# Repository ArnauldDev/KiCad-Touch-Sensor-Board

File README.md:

# Proto Board Touch-Sensor Controller

Top view of the [board with 3D rendering](https://forum.kicad.info/t/simple-tutorial-how-to-create-blender-3d-model-from-kicad/46485) generated with [Blender](https://www.blender.org/), see [Import PCB 3D Models from KiCad](https://extensions.blender.org/add-ons/pcb3d-importer/):

Bottom view of the board and 3D rendering generated with Blender too:

## AT42QT2120

Touch Sensor QTouch [AT42QT2120](https://www.microchip.com/en-us/product/at42qt2120): [view pdf datasheet online](https://ww1.microchip.com/downloads/en/DeviceDoc/doc9634.pdf)

AT42QT2120 is a 10-channel capacitive touch sensor controller with I2C interface.

It is designed for applications such as buttons, sliders, and wheels.

AT42QT2120-SU = 20 pin 0.300 inch wide body SOIC package

[Hole for Backlighting LED - page 13](https://ww1.microchip.com/downloads/aemDocuments/documents/OTH/ApplicationNotes/ApplicationNotes/Atmel-42094-QTouch-Schematic-and-Layout-Checklist_ApplicationNote_AT02259.pdf), see "Figure 3-2. Hole for Backlighting LED"

Example for [AT42QT_API](https://github.com/SmartTech/AT42QT/blob/master/AT42QT_API/QT2120.h)

## Demo board QT1 XPLAINED PRO EXTENSION KIT

Part Number: [ATQT1-XPRO](https://www.microchip.com/en-us/development-tool/ATQT1-XPRO)

[SAM D20 XPLAINED PRO EVALUATION KIT](https://ww1.microchip.com/downloads/aemDocuments/documents/OTH/ProductDocuments/UserGuides/Atmel-42102-SAMD20-Xplained-Pro_User-Guide.pdf)<br>
Part Number: [ATSAMD20-XPRO](https://www.microchip.com/en-us/development-tool/ATSAMD20-XPRO)

---

<br />

## SMD LED reverse mount

LED, Rouge, Vert jaune, CMS - Montage inversé, Rectangulaire, R 20mA, YG 20mA<br>
* [Farnell 2908898](https://fr.farnell.com/rohm/sml-822mv8wt86/led-rouge-jaune-vert-30-25mcd/dp/2908898)
* [Rohm Datasheet](https://fscdn.rohm.com/en/products/databook/datasheet/opto/led/chip_multi/sml-822mv8wt86-e.pdf)

|               Package view                | Reverse mount available, 2-color LED (Yellow-green/Red)                                                                                                                                                                                                                            |
| :---------------------------------------: | :--------------------------------------------------------------------------------------------------------------------------------------------------------------------------------------------------------------------------------------------------------------------------------- |
|  | Part Number: [SML-822MV8WT86](https://www.rohm.com/products/led/chip-leds-multi-color-type/sml-822mv8w-product)<br>SML-82 series is a two-color LED chip LED for back-mounting.<br>Rear mounting enables single-sided mounting, contributing to space saving in the mounting area. |

---

## Driver de LED DC/DC

### PCA9635PW,118

LED-Driver-PCA9635

> Code Commande Farnell : [1854073](https://fr.farnell.com/nxp/pca9635pw-118/driver-de-led-rgba-28-tssop/dp/1854073)
> Quantité 1, Prix (TVA incluse) 2,760€
> Driver LED, Bus I2C, Isolé, 16 bits, 1MHz, Sortie 5,5V/25mA, Entrée 2,3V à 5,5V
> https://fr.aliexpress.com/item/33038992925.html
> https://www.nxp.com/docs/en/data-sheet/PCA9635.pdf

[Breakout PCA9685PW module Servomotor Shield on Aliexpress](https://fr.aliexpress.com/item/1005007462728654.html)

<!--  -->

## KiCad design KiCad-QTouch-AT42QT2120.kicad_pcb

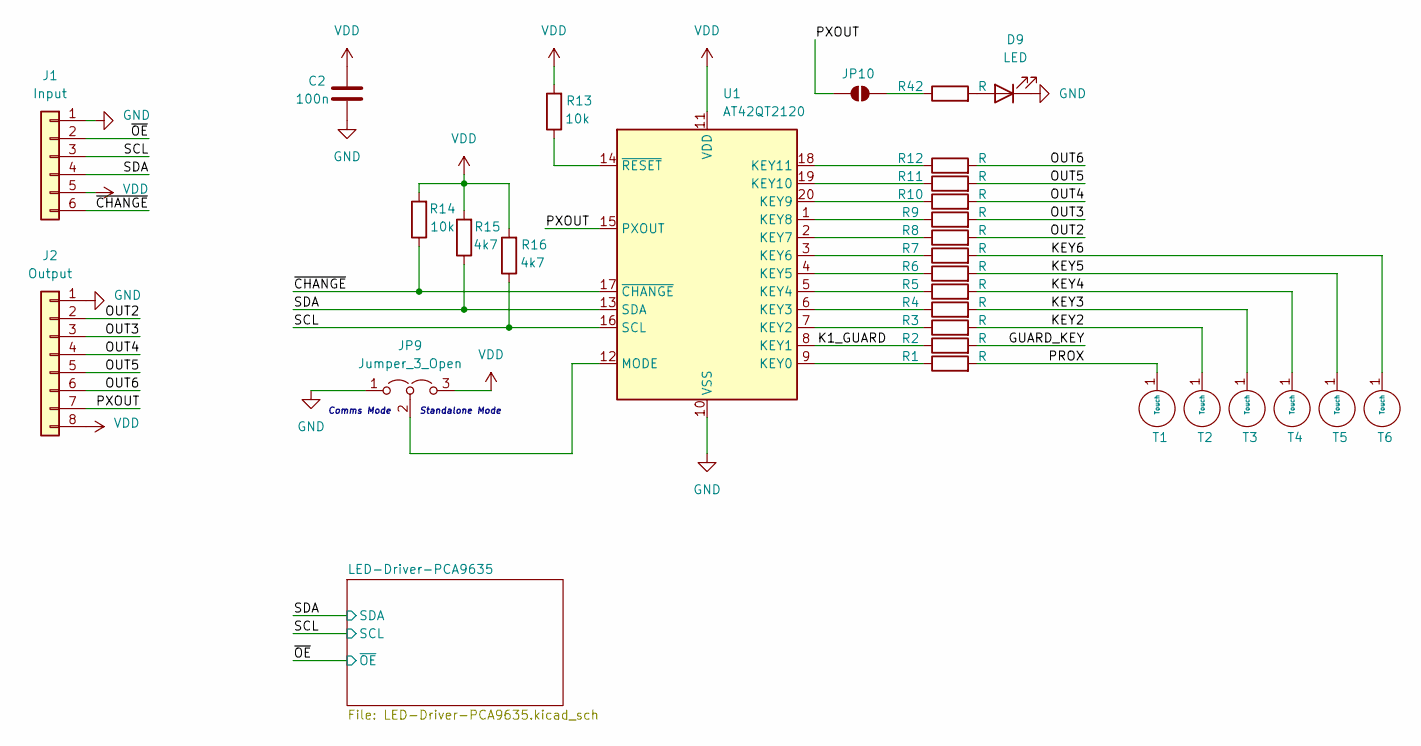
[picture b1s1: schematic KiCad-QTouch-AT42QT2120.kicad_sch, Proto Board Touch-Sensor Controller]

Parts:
C2: 100n; C_0805_2012Metric_Pad1.18x1.45mm_HandSolder
D9: LED; LED_0805_2012Metric_Pad1.15x1.40mm_HandSolder
J1: Input; PinHeader_1x06_P2.54mm_Vertical
J2: Output; PinHeader_1x08_P2.54mm_Vertical
JP9: Jumper_3_Open; SolderJumper-3_P2.0mm_Open_TrianglePad1.0x1.5mm
JP10: SolderJumper_2_Open; SolderJumper-2_P1.3mm_Open_TrianglePad1.0x1.5mm
R1, R2, R3, R4, R5, R6, R7, R8, R9, R10, R11, R12, R42: R; R_0805_2012Metric_Pad1.20x1.40mm_HandSolder
R13, R14: 10k; R_0805_2012Metric_Pad1.20x1.40mm_HandSolder
R15, R16: 4k7; R_0805_2012Metric_Pad1.20x1.40mm_HandSolder
T1, T2, T3, T4, T5, T6: Touch_12mm_round
U1: AT42QT2120; SOIC-20W_7.5x12.8mm_P1.27mm

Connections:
/GUARD_KEY: R2.2
/K1_GUARD: R2.1, U1.8 (KEY1)
/KEY2: R3.2, T2.1 (Touch)
/KEY3: R4.2, T3.1 (Touch)
/KEY4: R5.2, T4.1 (Touch)
/KEY5: R6.2, T5.1 (Touch)
/KEY6: R7.2, T6.1 (Touch)
/OUT2: J2.2, R8.2
/OUT3: J2.3, R9.2
/OUT4: J2.4, R10.2
/OUT5: J2.5, R11.2
/OUT6: J2.6, R12.2
/PROX: R1.2, T1.1 (Touch)
/PXOUT: J2.7, JP10.1 (A), U1.15 (PXOUT)
/SCL: J1.3, R16.1, U1.16 (SCL); also elsewhere on the board
/SDA: J1.4, R15.1, U1.13 (SDA); also elsewhere on the board
/~CHANGE: J1.6, R14.1, U1.17 (~CHANGE)
/~OE: J1.2; also elsewhere on the board
GND: C2.2, D9.1 (K), J1.1, J2.1, JP9.1 (A), U1.10 (VSS); also elsewhere on the board
unnamed: D9.2 (A), R42.2
unnamed: JP9.2 (C), U1.12 (MODE)
unnamed: JP10.2 (B), R42.1
unnamed: R1.1, U1.9 (KEY0)
unnamed: R3.1, U1.7 (KEY2)
unnamed: R4.1, U1.6 (KEY3)
unnamed: R5.1, U1.5 (KEY4)
unnamed: R6.1, U1.4 (KEY5)
unnamed: R7.1, U1.3 (KEY6)
unnamed: R8.1, U1.2 (KEY7)
unnamed: R9.1, U1.1 (KEY8)
unnamed: R10.1, U1.20 (KEY9)
unnamed: R11.1, U1.19 (KEY10)
unnamed: R12.1, U1.18 (KEY11)
unnamed: R13.1, U1.14 (~RESET)
VDD: C2.1, J1.5, J2.8, JP9.3 (B), R13.2, R14.2, R15.2, R16.2, U1.11 (VDD); also elsewhere on the board

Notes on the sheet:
Standalone Mode
Comms Mode

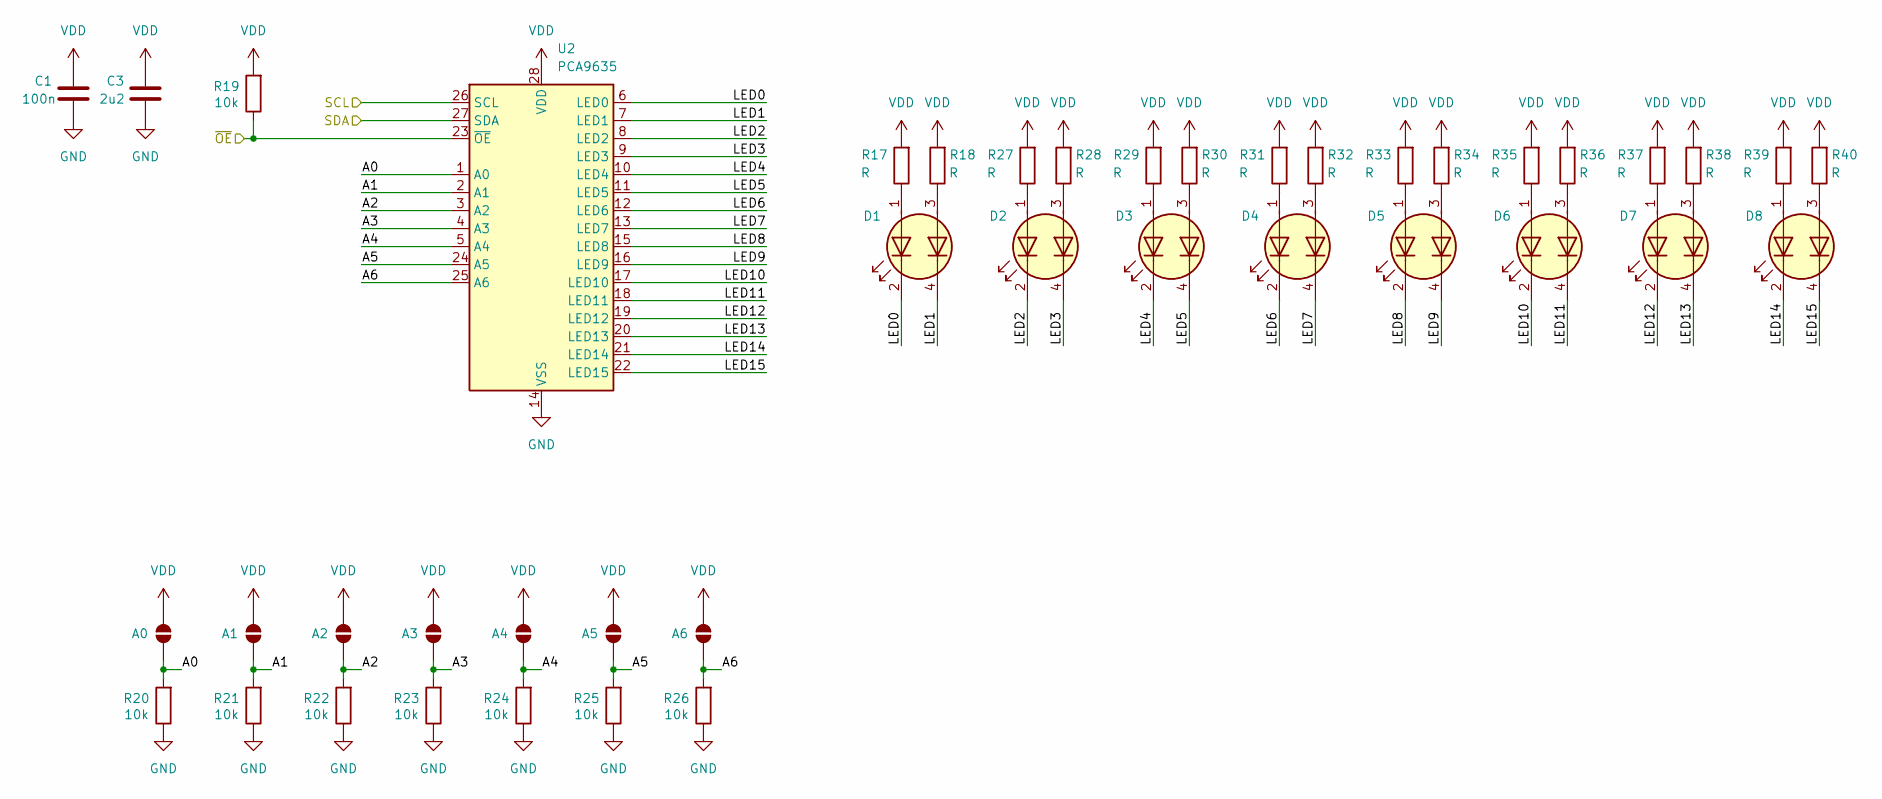
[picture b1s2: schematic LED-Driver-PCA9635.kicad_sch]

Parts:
A0, A1, A2, A3, A4, A5, A6: SolderJumper_2_Open; SolderJumper-2_P1.3mm_Open_TrianglePad1.0x1.5mm
C1: 100n; C_0805_2012Metric_Pad1.18x1.45mm_HandSolder
C3: 2u2; C_0805_2012Metric_Pad1.18x1.45mm_HandSolder
D1, D2, D3, D4, D5, D6, D7, D8: LED_Dual_AKAK; LED_SML-822MV8WT86
R17, R18, R27, R28, R29, R30, R31, R32, R33, R34, R35, R36, R37, R38, R39, R40: R; R_0805_2012Metric_Pad1.20x1.40mm_HandSolder
R19, R20, R21, R22, R23, R24, R25, R26: 10k; R_0805_2012Metric_Pad1.20x1.40mm_HandSolder
U2: PCA9635; TSSOP-28_4.4x9.7mm_P0.65mm

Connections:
/LED-Driver-PCA9635/A0: A0.2 (B), R20.2, U2.1 (A0)
/LED-Driver-PCA9635/A1: A1.2 (B), R21.2, U2.2 (A1)
/LED-Driver-PCA9635/A2: A2.2 (B), R22.2, U2.3 (A2)
/LED-Driver-PCA9635/A3: A3.2 (B), R23.2, U2.4 (A3)
/LED-Driver-PCA9635/A4: A4.2 (B), R24.2, U2.5 (A4)
/LED-Driver-PCA9635/A5: A5.2 (B), R25.2, U2.24 (A5)
/LED-Driver-PCA9635/A6: A6.2 (B), R26.2, U2.25 (A6)
/LED-Driver-PCA9635/LED0: D1.2 (K1), U2.6 (LED0)
/LED-Driver-PCA9635/LED1: D1.4 (K2), U2.7 (LED1)
/LED-Driver-PCA9635/LED2: D2.2 (K1), U2.8 (LED2)
/LED-Driver-PCA9635/LED3: D2.4 (K2), U2.9 (LED3)
/LED-Driver-PCA9635/LED4: D3.2 (K1), U2.10 (LED4)
/LED-Driver-PCA9635/LED5: D3.4 (K2), U2.11 (LED5)
/LED-Driver-PCA9635/LED6: D4.2 (K1), U2.12 (LED6)
/LED-Driver-PCA9635/LED7: D4.4 (K2), U2.13 (LED7)
/LED-Driver-PCA9635/LED8: D5.2 (K1), U2.15 (LED8)
/LED-Driver-PCA9635/LED9: D5.4 (K2), U2.16 (LED9)
/LED-Driver-PCA9635/LED10: D6.2 (K1), U2.17 (LED10)
/LED-Driver-PCA9635/LED11: D6.4 (K2), U2.18 (LED11)
/LED-Driver-PCA9635/LED12: D7.2 (K1), U2.19 (LED12)
/LED-Driver-PCA9635/LED13: D7.4 (K2), U2.20 (LED13)
/LED-Driver-PCA9635/LED14: D8.2 (K1), U2.21 (LED14)
/LED-Driver-PCA9635/LED15: D8.4 (K2), U2.22 (LED15)
/SCL: U2.26 (SCL); also elsewhere on the board
/SDA: U2.27 (SDA); also elsewhere on the board
/~OE: R19.1, U2.23 (~OE); also elsewhere on the board
GND: C1.2, C3.2, R20.1, R21.1, R22.1, R23.1, R24.1, R25.1, R26.1, U2.14 (VSS); also elsewhere on the board
unnamed: D1.1 (A1), R17.1
unnamed: D1.3 (A2), R18.1
unnamed: D2.1 (A1), R27.1
unnamed: D2.3 (A2), R28.1
unnamed: D3.1 (A1), R29.1
unnamed: D3.3 (A2), R30.1
unnamed: D4.1 (A1), R31.1
unnamed: D4.3 (A2), R32.1
unnamed: D5.1 (A1), R33.1
unnamed: D5.3 (A2), R34.1
unnamed: D6.1 (A1), R35.1
unnamed: D6.3 (A2), R36.1
unnamed: D7.1 (A1), R37.1
unnamed: D7.3 (A2), R38.1
unnamed: D8.1 (A1), R39.1
unnamed: D8.3 (A2), R40.1
VDD: A0.1 (A), A1.1 (A), A2.1 (A), A3.1 (A), A4.1 (A), A5.1 (A), A6.1 (A), C1.1, C3.1, R17.2, R18.2, R19.2, R27.2, R28.2, R29.2, R30.2, R31.2, R32.2, R33.2, R34.2, R35.2, R36.2, R37.2, R38.2, R39.2, R40.2, U2.28 (VDD); also elsewhere on the board

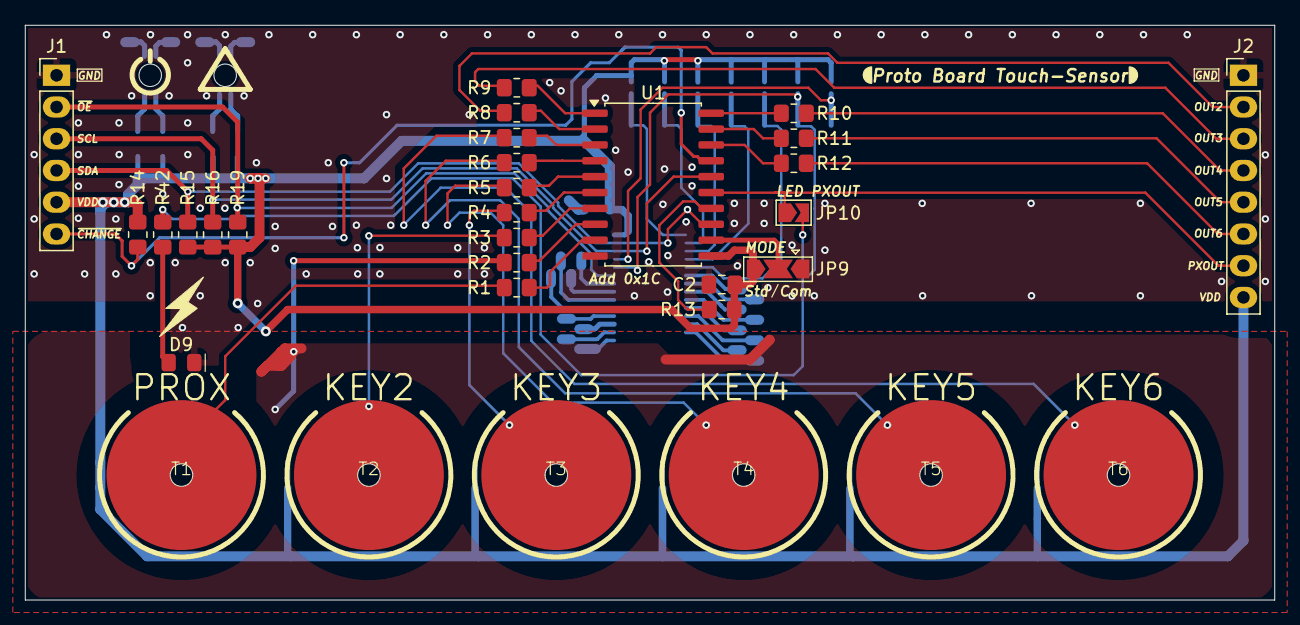
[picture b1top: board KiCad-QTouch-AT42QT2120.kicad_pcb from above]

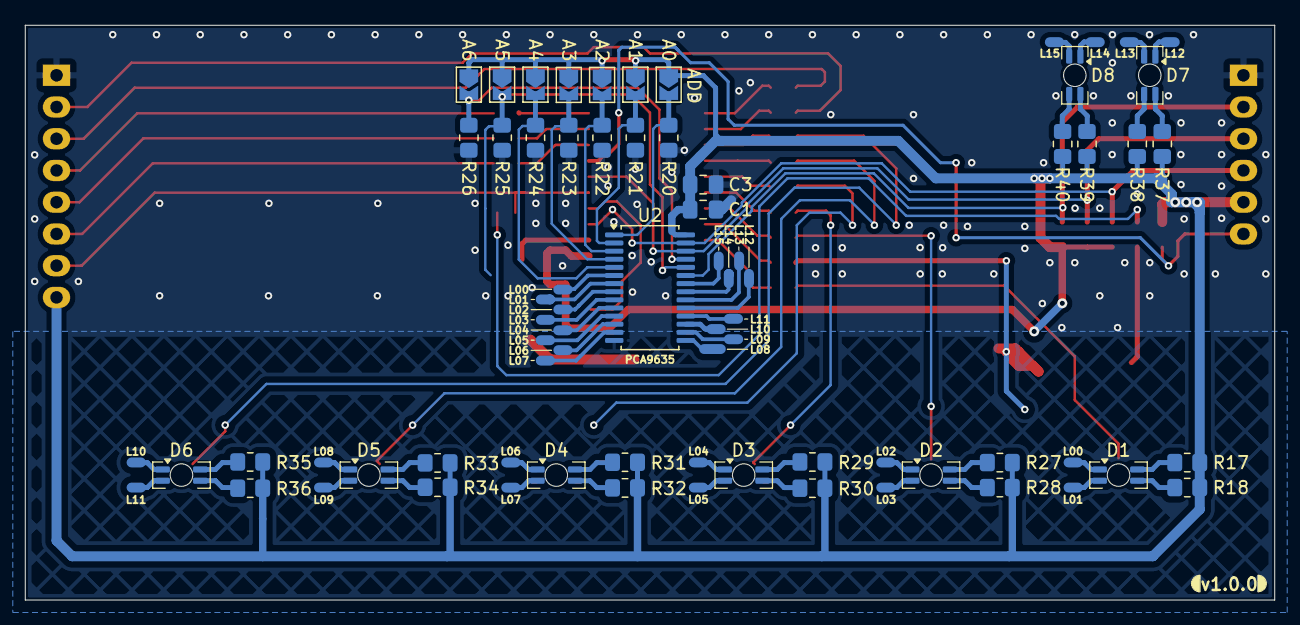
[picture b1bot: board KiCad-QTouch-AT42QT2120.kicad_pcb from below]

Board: 2 copper layers, 100.0 x 46.0 mm, 72 parts (41 on the bottom side), 73 nets.

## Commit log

2025-07-20 Project presentation
2025-07-20 KiCad project partage
2025-07-20 3D rendering generation with blender
2025-07-20 Add reverse mount LED
